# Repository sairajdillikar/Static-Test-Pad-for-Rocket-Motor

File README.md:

# Static-Test-Pad-for-Rocket-Motor

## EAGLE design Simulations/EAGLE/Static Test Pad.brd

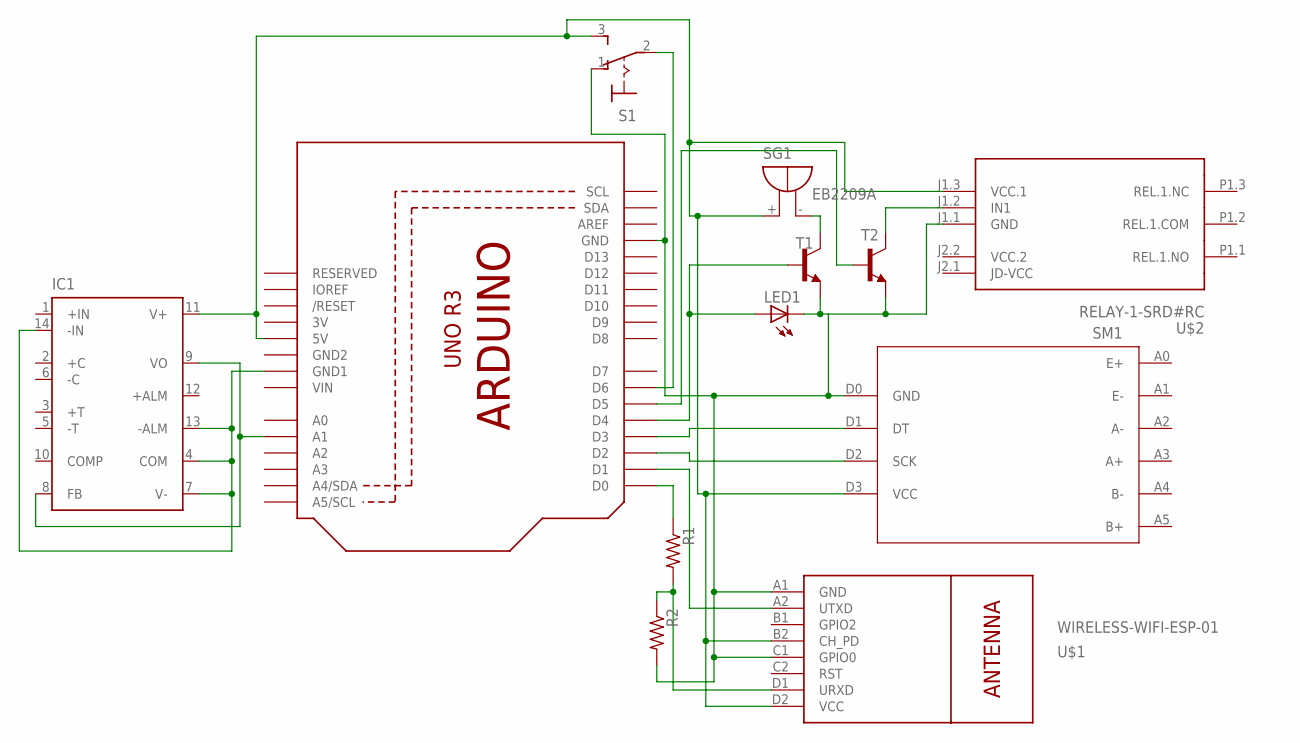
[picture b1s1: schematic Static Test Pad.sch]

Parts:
IC1: AD595; DIL14
LED1: LEDB155; Q62902-B155
R1, R2: FLIPFLOP-RES; 0805-THM
S1: 320-916
SG1: EB2209A
SM1: HX711
T1, T2: 2N3700-NPN-TO18-EBC; TO18
U1: ARDUINOR3-BPLACE
U$1: WIRELESS-WIFI-ESP-01
U$2: RELAY-1-SRD#RC

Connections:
3V: U1.3V
GND2: U1.GND2
unnamed: IC1.8 (FB), IC1.9 (VO), U1.A1
unnamed: IC1.4 (COM), IC1.7 (V-), IC1.13 (-ALM), IC1.14 (-IN), U1.GND1
unnamed: S1.2, U1.D6
unnamed: LED1.K (C), R2.2, S1.1 (O), SM1.D0 (GND), T1.1 (E), T2.1 (E), U1.GND, U$1.A1 (GND), U$1.C1 (GPIO0), U$2.J1.1 (GND)
unnamed: SG1.-, T1.3 (C)
unnamed: T2.2 (B), U1.D5
unnamed: LED1.A, T1.2 (B), U1.D4
unnamed: R1.2, R2.1, U$1.D1 (URXD)
unnamed: U1.D1, U$1.A2 (UTXD)
unnamed: T2.3 (C), U$2.J1.2 (IN1)
unnamed: SM1.D1 (DT), U1.D3
unnamed: SM1.D2 (SCK), U1.D2
unnamed: IC1.11 (V+), S1.3 (S), SG1.+, SM1.D3 (VCC), U1.5V, U$1.B2 (CH_PD), U$1.D2 (VCC), U$2.J1.3 (VCC.1)
unnamed: R1.1, U1.D0
VCC.2: U$2.J2.2 (VCC.2)
VIN: U1.VIN

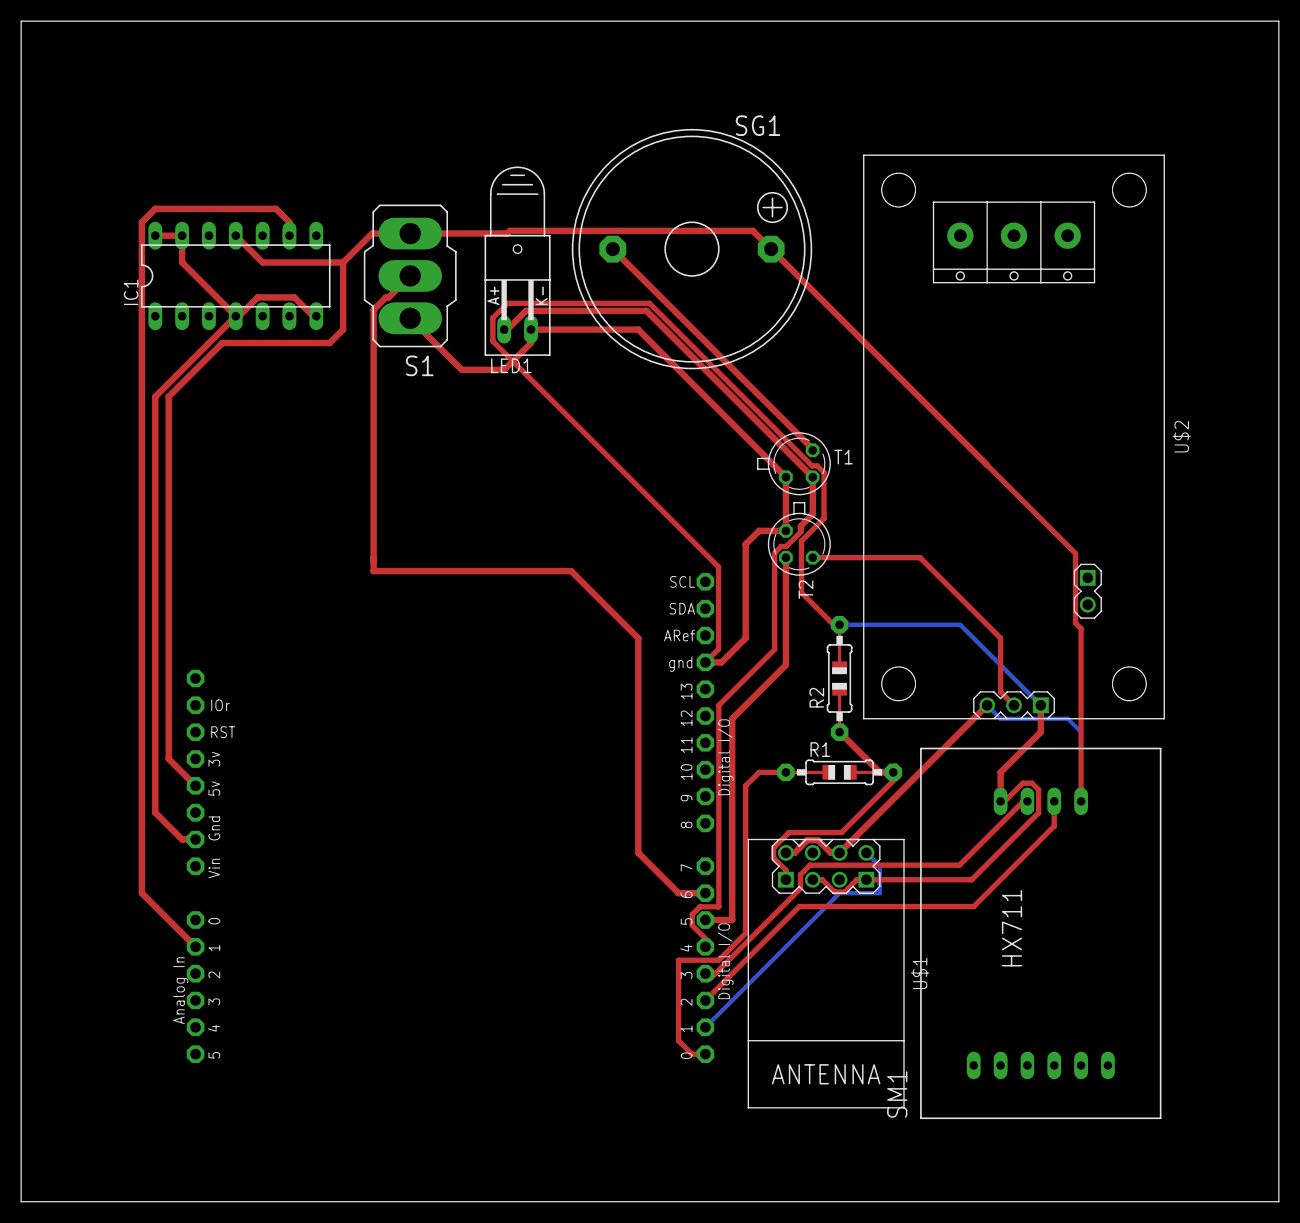
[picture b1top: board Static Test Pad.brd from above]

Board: 2 copper layers, 119.0 x 111.8 mm, 12 parts (0 on the bottom side), 14 nets.

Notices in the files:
parts and their libraries:
HC SR04: Released under the Creative Commons Attribution 4.0 International License: http://creativecommons.org/licenses/by/4.0
